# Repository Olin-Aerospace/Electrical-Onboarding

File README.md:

this project isn't late i promise

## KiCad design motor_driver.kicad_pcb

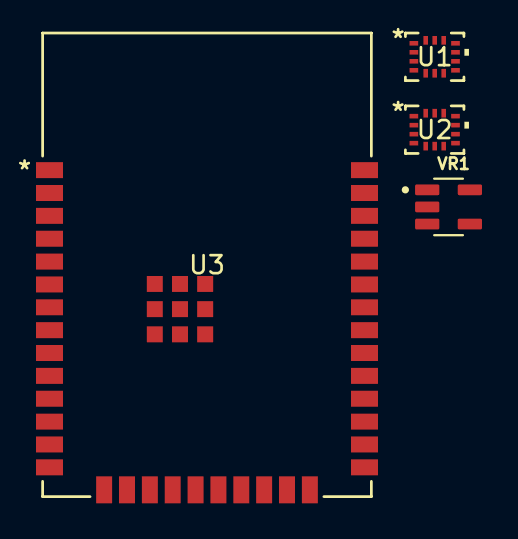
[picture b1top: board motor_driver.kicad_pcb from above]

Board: 2 copper layers, 4 parts (0 on the bottom side), 10 nets, no tracks yet.

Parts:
U1: DRV8210PDSGR; BMI323_BOS
U2: BMI323; BMI323_BOS
U3: ESP32-WROOM-32E 4MB; ESP32­WROOM­32E_EXP
VR1: AP7366-33W5-7; SOT95P285X140-5N

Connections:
/BAT: U1.1 (VM), VR1.1 (IN), VR1.3 (EN)
/VCC: U1.8 (VCC), U2.5 (VDDIO), U2.8 (VDD), U2.12 (CSB)
GND: U1.4 (GND), U1.9 (Thermal_Pad), U2.1 (SDO), U2.6 (GNDIO), U2.7 (GND), U3.1 (GND), U3.15 (GND), U3.38 (GND), U3.39 (GND), U3.40 (GND), U3.41 (GND), U3.42 (GND), U3.43 (GND), U3.44 (GND), U3.45 (GND), U3.46 (GND), U3.47 (GND), VR1.2 (GND)
unnamed: U1.6 (IN1), U3.35 (TXD0)
unnamed: U1.5 (IN2), U3.24 (IO2)
unnamed: U2.4 (INT1), U3.34 (RXD0)
unnamed: U2.9 (INT2), U3.29 (IO5)
unnamed: U2.13 (SCX), U3.26 (IO4)
unnamed: U2.14 (SDX), U3.27 (IO16)
unnamed: U3.2 (3V3), U3.3 (EN), VR1.5 (OUT)

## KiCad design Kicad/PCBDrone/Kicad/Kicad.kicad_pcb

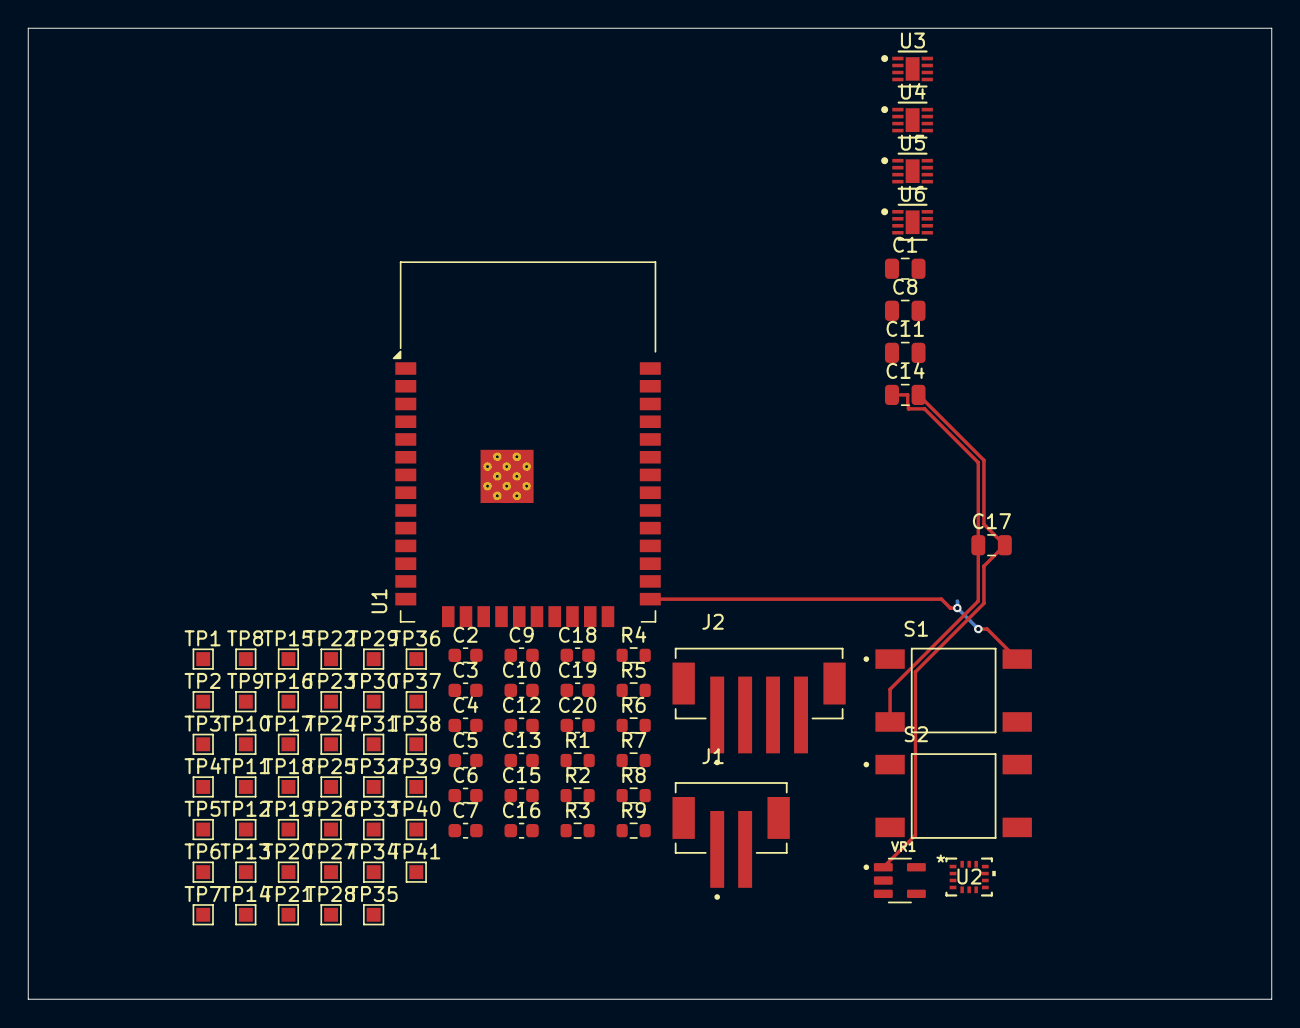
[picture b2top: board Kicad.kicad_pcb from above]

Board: 4 copper layers, 89.0 x 69.5 mm, 81 parts (0 on the bottom side), 35 nets.

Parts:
C1, C8, C11, C14, C17: 10uF; C_0805_2012Metric
C2, C3, C4, C5, C6, C7, C9, C10, C12, C13, C15, C16, C18, C19, C20: 0.1uF; C_0603_1608Metric
J1: Conn_01x02_Pin; JST_B2B-PH-SM4-TB
J2: Conn_01x04; JST_B4B-PH-SM4-TB
R1, R2, R3, R4, R5, R6, R7, R8, R9: 10k; R_0603_1608Metric
S1, S2: TS04-66-50-BK-260-SMT; SW_TS04-66-50-BK-260-SMT
TP1: IMU_SDA; TestPoint_Pad_1.0x1.0mm
TP2: IMU_SCL; TestPoint_Pad_1.0x1.0mm
TP3: IMU_CSB(UNUSED); TestPoint_Pad_1.0x1.0mm
TP4: IMU_VDD; TestPoint_Pad_1.0x1.0mm
TP5: IMU_INT2(UNUSED); TestPoint_Pad_1.0x1.0mm
TP6: IMU_GND; TestPoint_Pad_1.0x1.0mm
TP7: IMU_GNDIO; TestPoint_Pad_1.0x1.0mm
TP8: IMU_VDDIO; TestPoint_Pad_1.0x1.0mm
TP9: IMU_INT1(UNUSED); TestPoint_Pad_1.0x1.0mm
TP10: U3_VM; TestPoint_Pad_1.0x1.0mm
TP11: U3_VCC; TestPoint_Pad_1.0x1.0mm
TP12: U3_MODE; TestPoint_Pad_1.0x1.0mm
TP13: U3_IN1; TestPoint_Pad_1.0x1.0mm
TP14: U3_IN2; TestPoint_Pad_1.0x1.0mm
TP15: U3_OUT1; TestPoint_Pad_1.0x1.0mm
TP16: U3_OUT2; TestPoint_Pad_1.0x1.0mm
TP17: U3_GND; TestPoint_Pad_1.0x1.0mm
TP18: U4_VM; TestPoint_Pad_1.0x1.0mm
TP19: U4_VCC; TestPoint_Pad_1.0x1.0mm
TP20: U4_MODE; TestPoint_Pad_1.0x1.0mm
TP21: U4_IN1; TestPoint_Pad_1.0x1.0mm
TP22: U4_IN2; TestPoint_Pad_1.0x1.0mm
TP23: U4_GND; TestPoint_Pad_1.0x1.0mm
TP24: U4_OUT1; TestPoint_Pad_1.0x1.0mm
TP25: U4_OUT2; TestPoint_Pad_1.0x1.0mm
TP26: U5_VM; TestPoint_Pad_1.0x1.0mm
TP27: U5_VCC; TestPoint_Pad_1.0x1.0mm
TP28: U5_MODE; TestPoint_Pad_1.0x1.0mm
TP29: U5_IN1; TestPoint_Pad_1.0x1.0mm
TP30: U5_IN2; TestPoint_Pad_1.0x1.0mm
TP31: U5_GND; TestPoint_Pad_1.0x1.0mm
TP32: U5_OUT1; TestPoint_Pad_1.0x1.0mm
TP33: U5_OUT2; TestPoint_Pad_1.0x1.0mm
TP34: U6_VM; TestPoint_Pad_1.0x1.0mm
TP35: U6_VCC; TestPoint_Pad_1.0x1.0mm
TP36: U6_MODE; TestPoint_Pad_1.0x1.0mm
TP37: U6_IN1; TestPoint_Pad_1.0x1.0mm
TP38: U6_IN2; TestPoint_Pad_1.0x1.0mm
TP39: U6_GND; TestPoint_Pad_1.0x1.0mm
TP40: U6_OUT1; TestPoint_Pad_1.0x1.0mm
TP41: U6_OUT2; TestPoint_Pad_1.0x1.0mm
U1: ESP32-WROOM-32E; ESP32-WROOM-32D
U2: BMI323; BMI323_BOS
U3, U4, U5, U6: DRV8210DSGR; DSG0008A-IPC_A
VR1: AP7366; AP7366-33W5-7

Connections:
/BOOT: C19.1, S1.3, U1.25 (IO0)
/ESP_UART_RX: J2.2, U1.34 (RXD0/IO3)
/ESP_UART_TX: J2.3, U1.35 (TXD0/IO1)
/MOTOR1_INPUT1: TP13.1, U1.8 (IO32), U3.6 (IN1_PH)
/MOTOR1_INPUT2: TP14.1, U1.9 (IO33), U3.5 (IN2_EN)
/MOTOR1_NEG: TP16.1, U3.3 (OUT2)
/MOTOR1_POS: TP15.1, U3.2 (OUT1)
/MOTOR2_INPUT1: TP21.1, U1.30 (IO18), U4.6 (IN1_PH)
/MOTOR2_INPUT2: TP22.1, U1.10 (IO25), U4.5 (IN2_EN)
/MOTOR2_NEG: TP25.1, U4.3 (OUT2)
/MOTOR2_POS: TP24.1, U4.2 (OUT1)
/MOTOR3_INPUT1: TP29.1, U1.11 (IO26), U5.6 (IN1_PH)
/MOTOR3_INPUT2: TP30.1, U1.12 (IO27), U5.5 (IN2_EN)
/MOTOR3_NEG: TP33.1, U5.3 (OUT2)
/MOTOR3_POS: TP32.1, U5.2 (OUT1)
/MOTOR4_INPUT1: TP37.1, U1.13 (IO14), U6.6 (IN1_PH)
/MOTOR4_INPUT2: TP38.1, U1.28 (IO17), U6.5 (IN2_EN)
/MOTOR4_NEG: TP41.1, U6.3 (OUT2)
/MOTOR4_POS: TP40.1, U6.2 (OUT1)
/SCL: R9.2, TP2.1, U1.36 (IO22), U2.13 (SCX)
/SDA: R8.2, TP1.1, U1.33 (IO21), U2.14 (SDX)
/VBAT: C1.1, C2.2, C7.2, C8.2, C11.2, C12.2, C14.2, C15.2, C17.2, C18.2, J1.1, R1.2, TP10.1, TP18.1, TP26.1, TP34.1, U3.1 (VM), U4.1 (VM), U5.1 (VM), U6.1 (VM), VR1.1 (IN)
/VCC_3V3: C3.2, C4.2, C5.1, C6.1, C9.1, C10.1, C13.1, C16.1, J2.1, R2.1, R3.1, R4.1, R5.1, R6.1, R7.1, R8.1, R9.1, TP4.1, TP8.1, TP11.1, TP19.1, TP27.1, TP35.1, U1.2 (VDD), U2.5 (VDDIO), U2.8 (VDD), U3.8 (VCC), U4.8 (VCC), U5.8 (VCC), U6.8 (VCC), VR1.5 (OUT)
GND: C1.2, C2.1, C3.1, C4.1, C5.2, C6.2, C7.1, C8.1, C9.2, C10.2, C11.1, C12.1, C13.2, C14.1, C15.1, C16.2, C17.1, C18.1, C19.2, C20.2, J1.2, J2.4, S1.2, S2.2, TP6.1, TP7.1, TP17.1, TP23.1, TP31.1, TP39.1, U1.1 (GND), U1.15 (GND), U1.38 (GND), U1.39 (GND), U2.1 (SDO), U2.6 (GNDIO), U2.7 (GND), U3.4 (GND), U3.9 (Thermal_Pad), U4.4 (GND), U4.9 (Thermal_Pad), U5.4 (GND), U5.9 (Thermal_Pad), U6.4 (GND), U6.9 (Thermal_Pad), VR1.2 (GND)
unnamed: R2.2, S2.1
unnamed: R7.2, S1.1
unnamed: C20.1, S2.3, U1.3 (EN)
unnamed: TP3.1, U2.12 (CSB)
unnamed: TP9.1, U2.4 (INT1)
unnamed: TP5.1, U2.9 (INT2)
unnamed: R3.2, TP12.1, U3.7 (MODE)
unnamed: R4.2, TP20.1, U4.7 (MODE)
unnamed: R5.2, TP28.1, U5.7 (MODE)
unnamed: R6.2, TP36.1, U6.7 (MODE)
unnamed: R1.1, VR1.3 (EN)

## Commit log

2025-09-22 First commit, Added handouts
2025-09-22 Renamed file
2025-09-22 Changed name
2025-09-22 Rename Setup & Motor Driver Circuit.pdf to Handout 2: Setup & Motor Driver Circuit.pdf
2025-09-22 Rename Handout 1: PCB Drone Background.pdf to Handout1-PCB_Drone_Background.pdf
2025-09-22 Rename Handout 2: Setup & Motor Driver Circuit.pdf to Handout2-Setup&Motor_Driver_Circuit.pdf
2025-09-22 Rename Handout1-PCB_Drone_Background.pdf to Handouts/Handout1-PCB_Drone_Background.pdf
2025-09-22 Rename Handout2-Setup&Motor_Driver_Circuit.pdf to Handouts/Handout2-Setup&Motor_Driver_Circuit.pdf
2025-09-22 cleanup
2025-09-23 motor driver
2025-09-23 bing chilling but i have to add resistors and capacitors still
2025-09-23 tehe!
2025-09-23 test
2025-09-23 This is a test :D
2025-09-23 (helloworld.txt)
2025-09-23 first
2025-09-23 motor_driver
2025-09-27 all the joy in life has disappeared
2025-09-27 added footprints
2025-09-28 Updated Handout 2
2025-09-30 Hello. Also your hair is nice
2025-10-01 4 motors :fearful:
2025-10-03 Worked on the schematics
2025-10-21 Revision 2.3
2025-10-28 added pcb schematic
